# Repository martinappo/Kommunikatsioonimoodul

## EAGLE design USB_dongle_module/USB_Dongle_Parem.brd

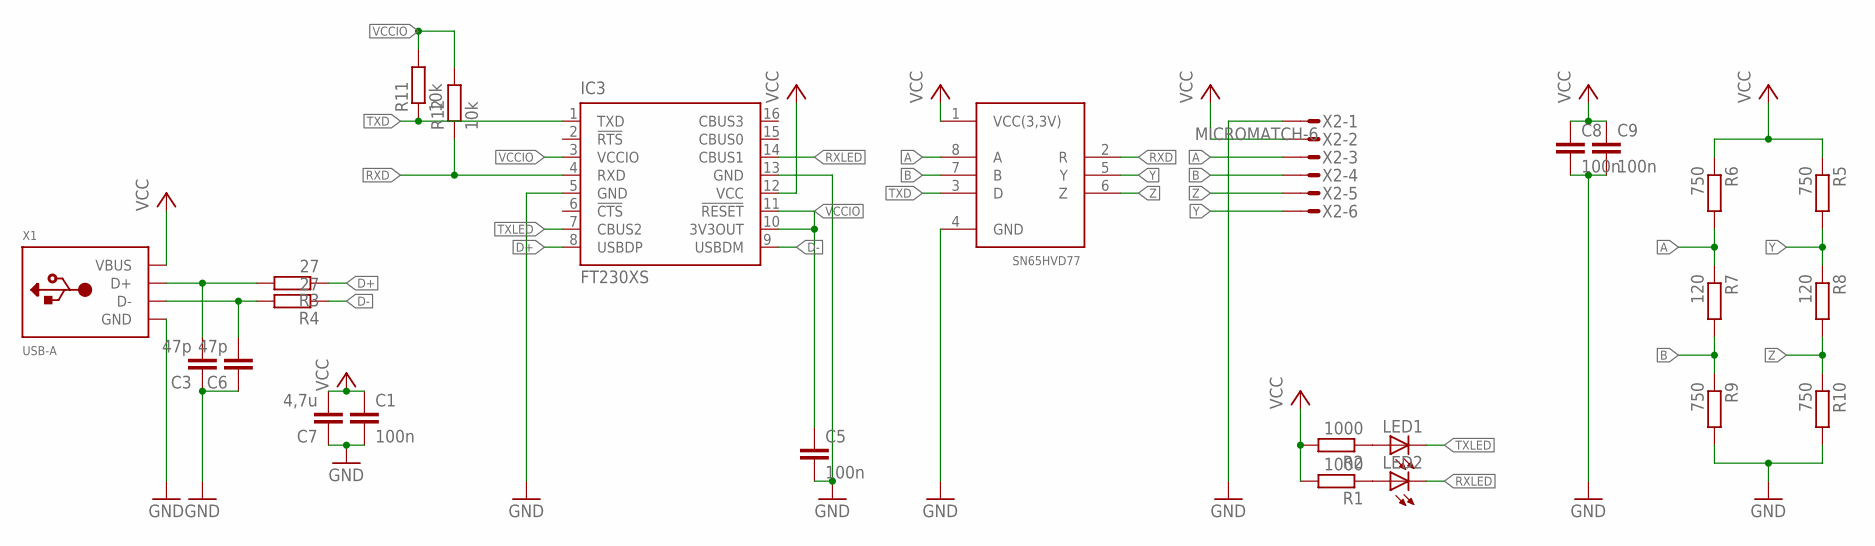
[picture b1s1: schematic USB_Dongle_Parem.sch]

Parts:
C1, C5, C8, C9: 100n; C0603
C3, C6: 47p; C0603
C7: 4,7u; C1206
IC3: FT230XS; SSOP16
LED1, LED2: LED_ESML0603; LED_SML0603
R1, R2: 1000; R0603
R3, R4: 27; R0603
R5, R6, R9, R10: 750; R0603
R7, R8: 120; R0603
R11, R12: 10k; R0603
U$2: SN65HVD77D; SOIC-8
X1: USB-A; MOLEX_480371000
X2: MICROMATCH-6

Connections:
A: R6.2, R7.1, U$2.8 (A), X2.3
B: R7.2, R9.1, U$2.7 (B), X2.4
D+: IC3.8 (USBDP), R3.1
D-: IC3.9 (USBDM), R4.1
GND: C1.2, C3.1, C5.2, C6.1, C7.1, C8.2, C9.2, IC3.5 (GND), IC3.13 (GND), R9.2, R10.2, U$2.4 (GND), X1.4 (GND), X2.1
unnamed: LED2.A, R1.1
unnamed: LED1.A, R2.1
RXD: IC3.4 (RXD), R12.1, U$2.2 (R)
RXLED: IC3.14 (CBUS1), LED2.C
SA: C3.2, R3.2, X1.3 (D+)
SAD: C6.2, R4.2, X1.2 (D-)
TXD: IC3.1 (TXD), R11.1, U$2.3 (D)
TXLED: IC3.7 (CBUS2), LED1.C
VCC: C1.1, C7.2, C8.1, C9.1, IC3.12 (VCC), R1.2, R2.2, R5.1, R6.1, U$2.1 (VCC(3,3V)), X1.1 (VBUS), X2.2
VCCIO: C5.1, IC3.3 (VCCIO), IC3.10 (3V3OUT), IC3.11 (!RESET), R11.2, R12.2
Y: R5.2, R8.1, U$2.5 (Y), X2.6
Z: R8.2, R10.1, U$2.6 (Z), X2.5

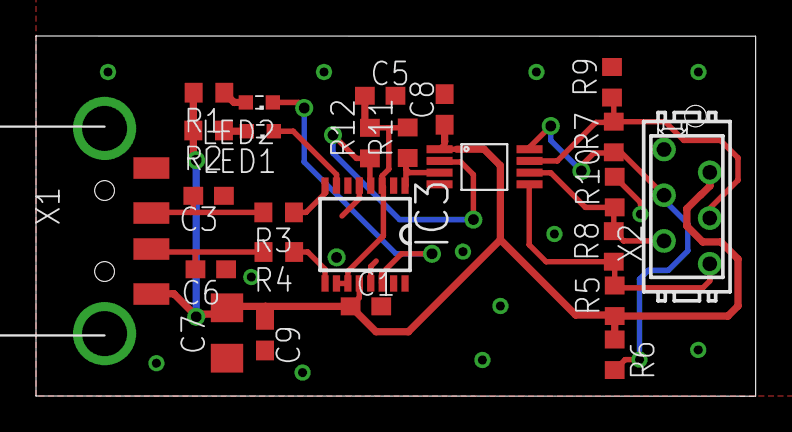
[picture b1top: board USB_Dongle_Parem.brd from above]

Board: 2 copper layers, 40.0 x 20.0 mm, 25 parts (0 on the bottom side), 17 nets.

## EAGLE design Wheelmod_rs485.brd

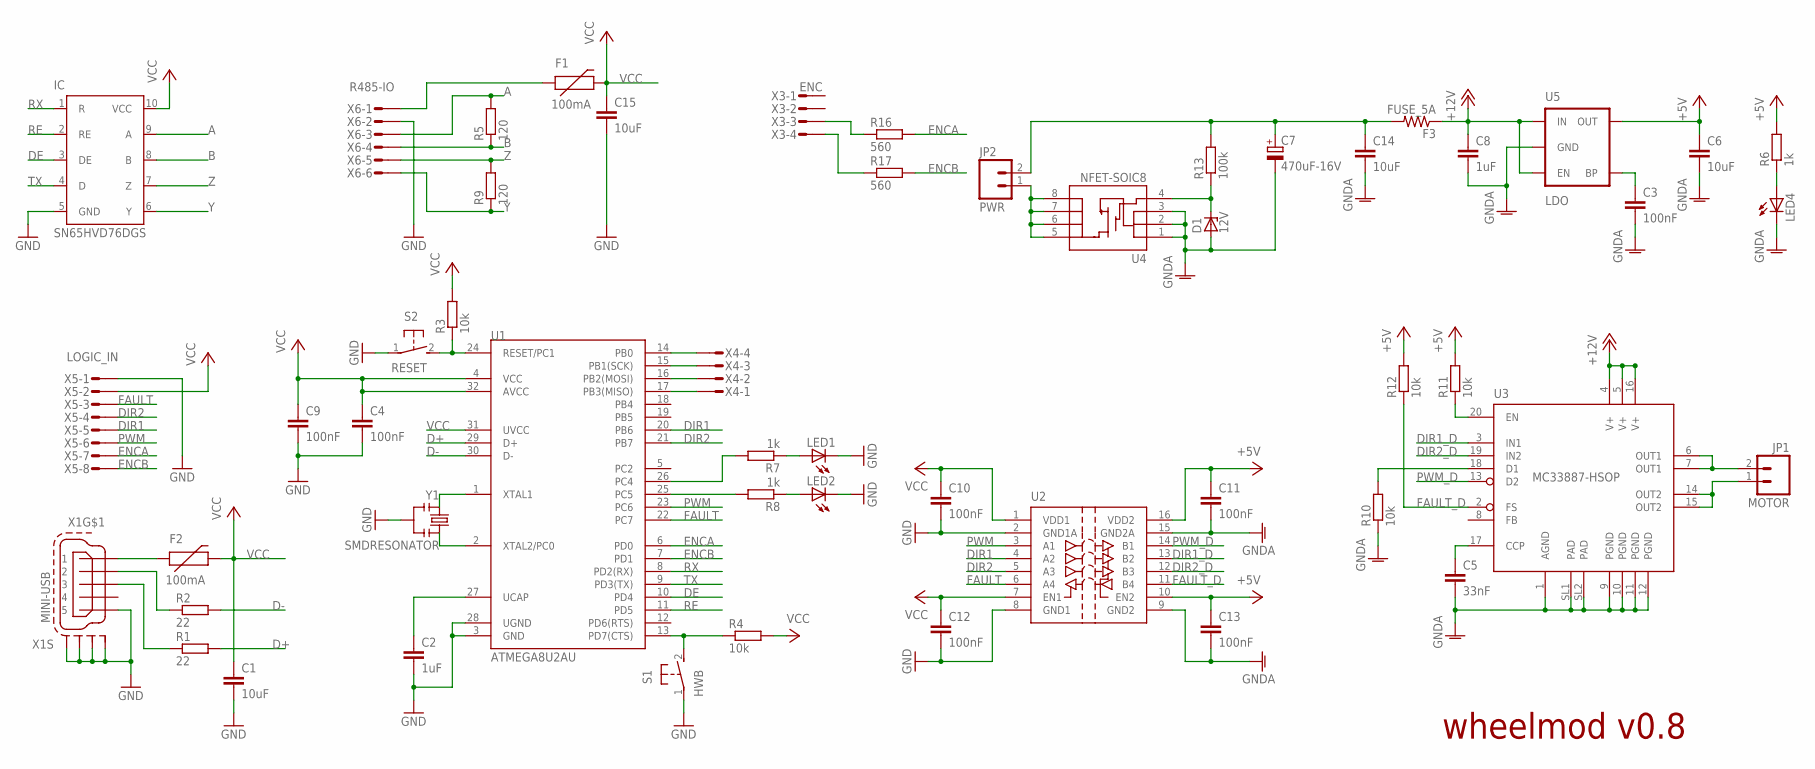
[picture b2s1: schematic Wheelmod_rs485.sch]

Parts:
C1, C6, C14, C15: 10uF; C1206K
C2, C8: 1uF; C0603K
C3, C4, C9, C10, C11, C12, C13: 100nF; C0603K
C5: 33nF; C0603K
C7: 470uF-16V; E3,5-8
D1: 12V; SOD123
F1, F2: 100mA; PTC-1206
F3: FUSE_5A; R1206
JP1: MOTOR; SCREWTERMINAL-3.5MM-2
JP2: PWR; SCREWTERMINAL-3.5MM-2
LED1, LED2, LED4: LEDCHIP-LED0603; CHIP-LED0603
R1, R2: 22; R0603
R3, R4, R10, R11, R12: 10k; R0603
R5, R9: 120; R0603
R6, R7, R8: 1k; R0603
R13: 100k; R0603
R16, R17: 560; R0603
S1: HWB; ADTSM3
S2: RESET; ADTSM3
U1: ATMEGA8U2AU; TQFP32-08
U2: SI8441IS1; SO16
U3: MC33887-HSOP; HSOP
U4: NFET-SOIC8; SO08
U5: LDO; SOT23-5
U$1: SN65HVF76DGS; MSOP10
X1: MINI-USB; 32005-301
X3: ENC; MICROMATCH-4
X4: MICROMATCH-4
X5: LOGIC_IN; MICROMATCH-8
X6: R485-IO; MICROMATCH-6
Y1: SMDRESONATOR; PBRC-M

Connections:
+5V: C6.1, C11.1, C13.1, R6.2, R11.2, R12.2, U2.10 (EN2), U2.16 (VDD2), U5.5 (OUT)
+12V: C8.1, F3.1, U3.4 (V+), U3.5 (V+), U3.16 (V+), U5.1 (IN), U5.3 (EN)
A: R5.2, U$1.9 (A), X6.3
B: R5.1, U$1.8 (B), X6.4
D+: R1.2, U1.29 (D+)
D-: R2.2, U1.30 (D-)
DE: U1.10 (PD4), U$1.3 (DE)
DIR1: U1.20 (PB6), U2.4 (A2), X5.5
DIR1_D: U2.13 (B2), U3.3 (IN1)
DIR2: U1.21 (PB7), U2.5 (A3), X5.4
DIR2_D: U2.12 (B3), U3.19 (IN2)
ENCA: R16.2, U1.6 (PD0), X5.7
ENCB: R17.2, U1.7 (PD1), X5.8
FAULT: U1.22 (PC7), U2.6 (A4), X5.3
FAULT_D: R12.1, U2.11 (B4), U3.2 (FS)
GND: C1.2, C2.2, C4.2, C9.2, C10.2, C12.2, C15.2, LED1.C, LED2.C, S1.1, S2.1, U1.3 (GND), U1.28 (UGND), U2.2 (GND1A), U2.8 (GND1), U$1.5 (GND), X1.5, X1.M1 (S1), X1.M2 (S2), X1.M3 (S3), X1.M4 (S4), X5.1, X6.2, Y1.2
GNDA: C3.2, C5.2, C6.2, C7.-, C8.2, C11.2, C13.2, C14.2, D1.A, LED4.C, R10.1, U2.9 (GND2), U2.15 (GND2A), U3.1 (AGND), U3.9 (PGND), U3.10 (PGND), U3.11 (PGND), U3.12 (PGND), U3.SL1 (PAD), U3.SL2 (PAD), U4.1 (S), U4.2 (S), U4.3 (S), U5.2 (GND)
unnamed: C2.1, U1.27 (UCAP)
unnamed: R4.1, S1.2, U1.13 (PD7(CTS))
unnamed: LED1.A, R7.1
unnamed: LED2.A, R8.1
unnamed: R1.1, X1.3
unnamed: F2.1, X1.1
unnamed: R2.1, X1.2
unnamed: U1.1 (XTAL1), Y1.1
unnamed: U1.2 (XTAL2/PC0), Y1.3
unnamed: R3.1, S2.2, U1.24 (RESET/PC1)
unnamed: C3.1, U5.4 (BP)
unnamed: R8.2, U1.25 (PC5)
unnamed: LED4.A, R6.1
unnamed: C5.1, U3.17 (CCP)
unnamed: R11.1, U3.20 (EN)
unnamed: R10.2, U3.18 (D1)
unnamed: R7.2, U1.26 (PC4)
unnamed: D1.C, R13.1, U4.4 (G)
unnamed: JP2.1, U4.5 (D), U4.6 (D), U4.7 (D), U4.8 (D)
unnamed: JP1.2, U3.6 (OUT1), U3.7 (OUT1)
unnamed: U1.14 (PB0), X4.4
unnamed: JP1.1, U3.14 (OUT2), U3.15 (OUT2)
unnamed: U1.15 (PB1(SCK)), X4.3
unnamed: U1.16 (PB2(MOSI)), X4.2
unnamed: R16.1, X3.3
unnamed: R17.1, X3.4
unnamed: C7.+, C14.1, F3.2, JP2.2, R13.2
unnamed: U1.17 (PB3(MISO)), X4.1
unnamed: F1.1, X6.1
PWM: U1.23 (PC6), U2.3 (A1), X5.6
PWM_D: U2.14 (B1), U3.13 (D2)
RE: U1.11 (PD5), U$1.2 (RE)
RX: U1.8 (PD2(RX)), U$1.1 (R)
TX: U1.9 (PD3(TX)), U$1.4 (D)
VCC: C1.1, C4.1, C9.1, C10.1, C12.1, C15.1, F1.2, F2.2, R3.2, R4.2, U1.4 (VCC), U1.31 (UVCC), U1.32 (AVCC), U2.1 (VDD1), U2.7 (EN1), U$1.10 (VCC), X5.2
Y: R9.1, U$1.6 (Y), X6.6
Z: R9.2, U$1.7 (Z), X6.5

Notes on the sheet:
wheelmod v0.8

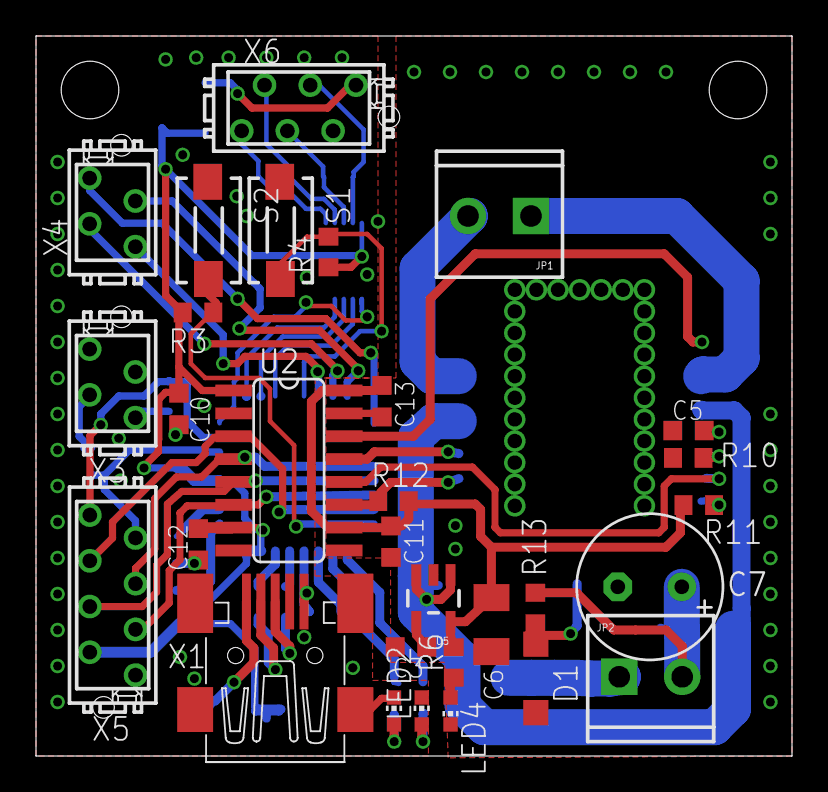
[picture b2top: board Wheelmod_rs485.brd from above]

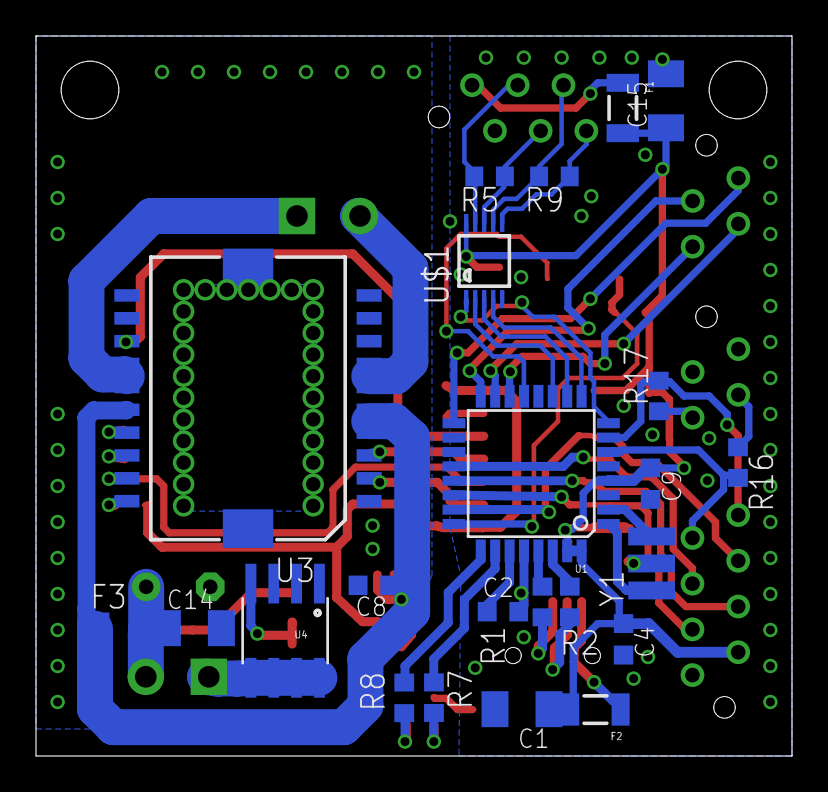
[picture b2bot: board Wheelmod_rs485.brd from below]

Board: 2 copper layers, 42.0 x 40.0 mm, 53 parts (23 on the bottom side), 54 nets.

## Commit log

2015-03-31 Some fixes done
    Termination resistor changed to correct placement and value. Micromatch
    moved not to obstruct screw.
2015-04-01 Testing
2015-04-01 Testing2
2015-04-12 Final changes
    Moved 2 components from bottom to top to make room for easier
    installment of board.
2015-04-13 Gerber files added
2015-04-13 Revert "Gerber files added"
    This reverts commit c41a4776acd19013353cf659853176ad3095f8b7.
2015-04-13 Revert "Revert "Gerber files added""
    This reverts commit a0782db79ab039ec4e8c756b3c31f73e9d3c7c26.
2015-06-08 Some changes to board and gerber files for production.
2015-08-04 Skeem
    Lisasin pooliku skeemi USB-kommunikatsiooni jubinast.
2015-08-04 Libra FULLDUPLEX komponendile
2015-08-04 Skeem
    Skeem valmis, vaja lisada nimetused ja väärtused
2015-08-09 Full duplex tugi kommunikatsioonimoodulit
2015-08-09 mikromatch augud
2015-08-10 Teine skeem
    Reiko poolt jagatud skeem, enne boardi tegemist vajab ülevaatamist.
2015-08-11 Board
    Board olemas, veidi vajab veel üle vaatamist, kuid oelemas siiski.
2015-08-12 Korrastasin boardi
    Tegin mõned muudatused skeemis ning korrastasin boardi. Valmis!
2015-08-13 Pinheader>Micromatch
    Vahetasin siis komponendi välja, lisaks muutsin kondekate asukohta.
2015-08-20 Minor fixes

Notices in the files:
parts and their libraries:
SparkFun: Licensing: CC v3.0 Share-Alike You are welcome to use this library for commercial purposes.
